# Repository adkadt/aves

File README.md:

<div align="center">

# AVES
### Aerospace Vehicle Embedded Suite

*A personal collection of avionics projects for model rocketry.*

</div>

---

## Overview

AVES is a collection of hardware and software projects developed for model rockets. The goal is to design reliable, flight-ready avionics while documenting the engineering process along the way.

Each project is developed independently and focuses on solving a specific problem, such as flight computers, telemetry, or tracking.

---

## Projects

| Project | Description | Status |
|---------|-------------|--------|
| **Pigeon** | GPS and LoRa tracker for rocket recovery | In Development |
| **Shrike** | Dual-deployment flight computer and altimeter | Early Development |
| **Wren** | Dual-deployment flight computer with integrated IMU and altimeter | Early Development |
| **GPS Ground Station** | Microcontroller-based LoRa receiver for displaying GPS telemetry | In Development |

---

## Goals

- Build reliable avionics for model rockets
- Learn through hands-on embedded development
- Produce well-documented hardware and firmware
- Keep projects maintainable and easy to understand

---

## Technologies

Projects within AVES make use of technologies such as:

- C++
- PlatformIO
- ESP32
- GPS
- LoRa
- Barometric sensors
- IMUs

The exact hardware varies by project.

---

## Repository Layout

```
AVES/
├── gps-ground-station/
├── pigeon/
├── shrike/
├── wren/
└── README.md
```

Each project contains its own firmware and documentation.

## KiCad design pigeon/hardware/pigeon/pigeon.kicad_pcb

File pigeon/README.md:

# Pigeon

Pigeon is a lightweight GPS and LoRa tracker built around the ESP32-S3. It is designed to provide reliable location tracking of landed model rockets.
## Features

- GPS position tracking
- LoRa communication
- Low-power friendly architecture

## Hardware

Current target platform:

- Waveshare ESP32-S3-Zero
- Adafruit Ultimate GPS
- Adafruit LoRa Radio
- WS2812 Status LED

## Project Structure

```
pigeon/
├── firmware/
│   ├── include/
│   ├── src/
│   └── platformio.ini
└── hardware/
```

## Firmware Design

The firmware is organized into independent modules.

- **LED** – Status indication and animations
- **GPS** – Position acquisition and parsing
- **LoRa** – Packet transmission and reception

Each module exposes a small public interface while hiding implementation details internally.

## Building

This project uses PlatformIO.

```bash
cd firmware
pio run
```

To upload:

```bash
pio run --target upload
```

To open the serial monitor:

```bash
pio device monitor
```

## Roadmap

- [x] Project structure
- [x] LED driver
- [ ] GPS integration
- [ ] LoRa communication

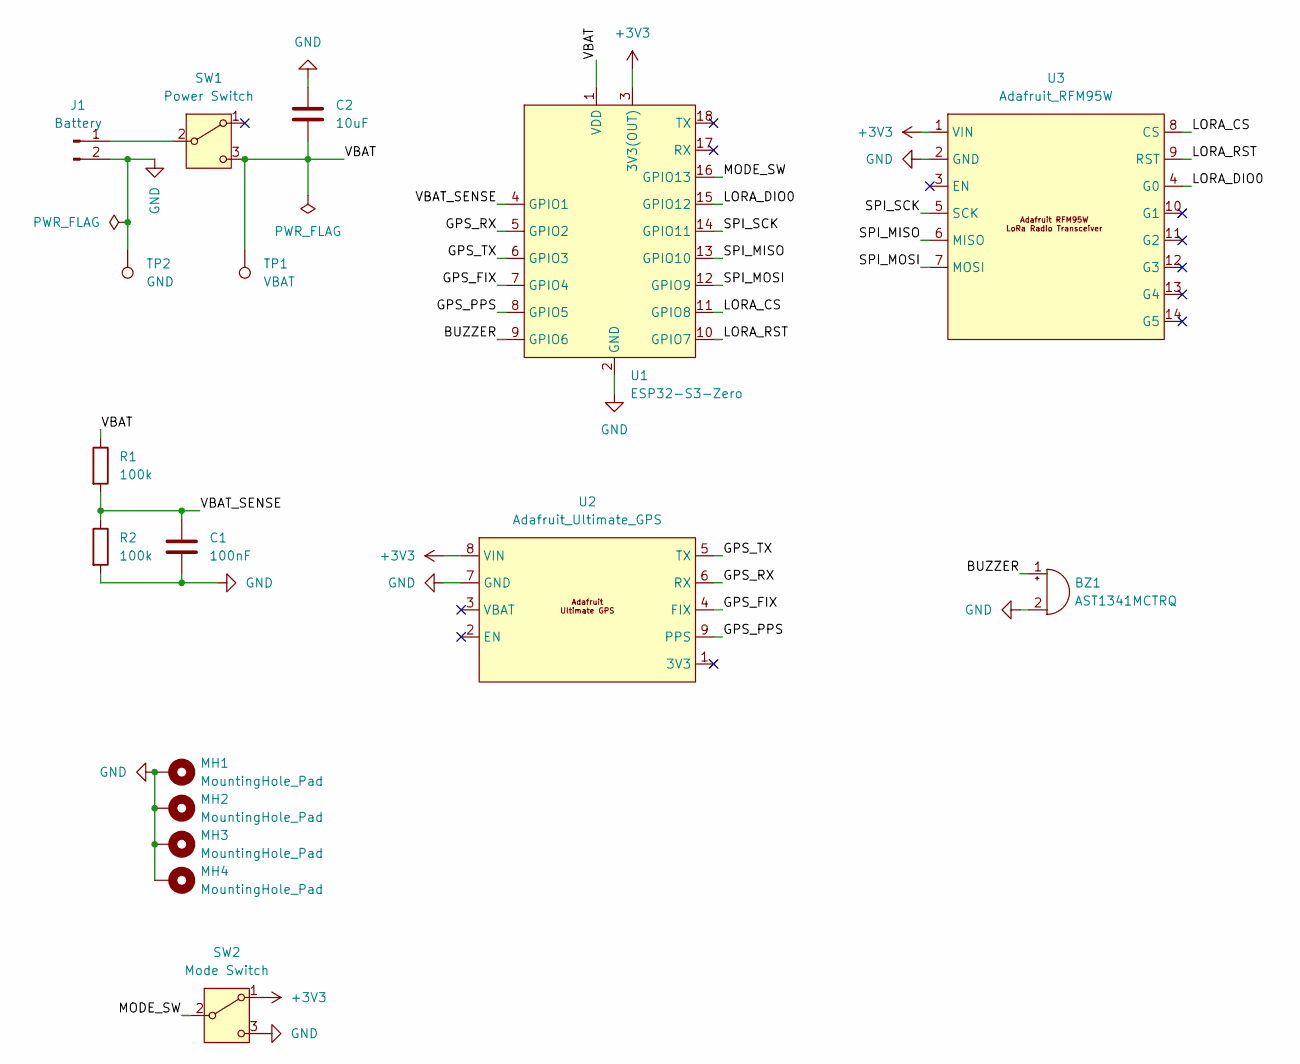
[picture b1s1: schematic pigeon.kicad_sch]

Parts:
BZ1: AST1341MCTRQ; BZ_AST1341MCTRQ
C1: 100nF; C_0805_2012Metric_Pad1.18x1.45mm_HandSolder
C2: 10uF; C_0805_2012Metric_Pad1.18x1.45mm_HandSolder
J1: Battery; JST_PH_S2B-PH-K_1x02_P2.00mm_Horizontal
MH1, MH2, MH3, MH4: MountingHole_Pad; MountingHole_2.2mm_M2_Pad_Via
R1, R2: 100k; R_0805_2012Metric_Pad1.20x1.40mm_HandSolder
SW1: Power Switch; SW_CK_JS102011SAQN
SW2: Mode Switch; SW_CK_JS102011SAQN
TP1: VBAT; TestPoint_Pad_D2.0mm
TP2: GND; TestPoint_Pad_D2.0mm
U1: ESP32-S3-Zero; Waveshare-ESP32-S3-Zero
U2: Adafruit_Ultimate_GPS
U3: Adafruit_RFM95W

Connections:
+3V3: SW2.1 (A), U1.3 (3V3(OUT)), U2.8 (VIN), U3.1 (VIN)
/BUZZER: BZ1.1 (+), U1.9 (GPIO6)
/GPS_FIX: U1.7 (GPIO4), U2.4 (FIX)
/GPS_PPS: U1.8 (GPIO5), U2.9 (PPS)
/GPS_RX: U1.5 (GPIO2), U2.6 (RX)
/GPS_TX: U1.6 (GPIO3), U2.5 (TX)
/LORA_CS: U1.11 (GPIO8), U3.8 (CS)
/LORA_DIO0: U1.15 (GPIO12), U3.4 (G0)
/LORA_RST: U1.10 (GPIO7), U3.9 (RST)
/MODE_SW: SW2.2 (B), U1.16 (GPIO13)
/SPI_MISO: U1.13 (GPIO10), U3.6 (MISO)
/SPI_MOSI: U1.12 (GPIO9), U3.7 (MOSI)
/SPI_SCK: U1.14 (GPIO11), U3.5 (SCK)
/VBAT: C2.2, R1.1, SW1.3 (C), TP1.1 (1_1), U1.1 (VDD)
/VBAT_SENSE: C1.1, R1.2, R2.1, U1.4 (GPIO1)
GND: BZ1.2 (-), C1.2, C2.1, J1.2, MH1.1 (1_1), MH2.1 (1_1), MH3.1 (1_1), MH4.1 (1_1), R2.2, SW2.3 (C), TP2.1 (1_1), U1.2 (GND), U2.7 (GND), U3.2 (GND)
unnamed: J1.1, SW1.2 (B)

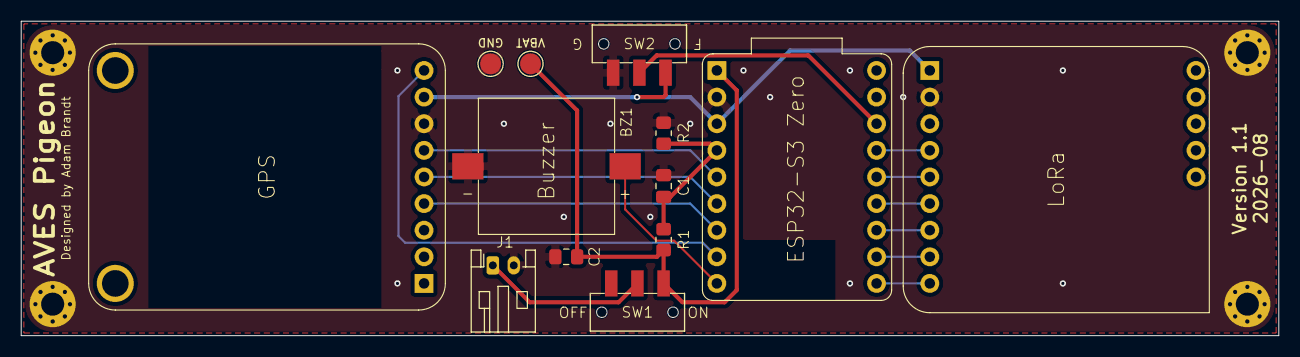
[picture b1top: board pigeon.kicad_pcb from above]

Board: 2 copper layers, 120.0 x 30.0 mm, 17 parts (0 on the bottom side), 17 nets.

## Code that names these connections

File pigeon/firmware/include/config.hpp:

#pragma once

#include <cstdint>
#include "system/system.hpp"

namespace Config {
    // This hardware revision has no physical mode switch.
    constexpr bool MODE_SWITCH_ENABLED = false;
    constexpr System::Mode PRIMARY_MODE = System::Mode::FLIGHT; // FLIGHT
    constexpr System::Mode SECONDARY_MODE = System::Mode::GROUND; // GROUND

    // Serial Config
    constexpr uint32_t BAUD_RATE = 115200;

    constexpr uint8_t DEVICE_ID = 1;
    constexpr uint8_t PAIRED_DEVICE_ID = 2;
    
    // GPS Config
    namespace GPS {
        constexpr uint32_t BAUD_RATE = 9600;
        constexpr uint32_t TIMEOUT_MS = 3000;
    
        // EMA
        constexpr double POSITION_ALPHA = 0.25;
    }

    // LoRa Config
    namespace LoRa {
        constexpr uint8_t MAX_PAYLOAD_LENGTH = 64;
        constexpr uint8_t PACKET_HEADER_LENGTH = 5; // this value is based on code [don't change]
        constexpr uint8_t MAX_PACKET_LENGTH = LoRa::MAX_PAYLOAD_LENGTH + LoRa::PACKET_HEADER_LENGTH;
    
        // LoRa Radio
        constexpr float FREQUENCY = 915.0;
        constexpr float BANDWIDTH = 125.0;
        constexpr uint8_t SPREADING_FACTOR = 9;
        constexpr uint8_t CODING_RATE = 7;
        constexpr uint8_t SYNC_WORD = 0x12;
        constexpr int8_t TX_POWER = 10;
        constexpr uint8_t PREAMBLE_LENGTH = 8;
        constexpr uint8_t GAIN = 0;
    } 

    // Battery
    namespace Battery {
        // Voltage divider
        constexpr float DIVIDER_TOP_RESISTOR = 100000.0f;
        constexpr float DIVIDER_BOTTOM_RESISTOR = 100000.0f;
        
        // Sampling
        constexpr uint32_t SAMPLE_INTERVAL_MS = 100; 

        // Battery Thresholds
        constexpr float MIN_USB_VOLTAGE = 4.7f;
        constexpr float LOW_VOLTAGE = 3.6f;
        constexpr float CRITICAL_VOLTAGE = 3.3f;
        constexpr float MEASURE_THRESHOLD_VOLTAGE = 1.0f;

        // EMA
        constexpr float VOLTAGE_FILTER_ALPHA  = 0.3f;
    }

    namespace Flight {
        constexpr uint32_t HEARTBEAT_INTERVAL = 15000;
        constexpr uint32_t GPS_TELEMETRY_INTERVAL = 1000;
    }

    namespace Ground {
        constexpr uint32_t CONNECTION_TIMEOUT = 60000;
    }
}

namespace Pins {
    // LED
    constexpr uint8_t LED = 21;
    
    // GPS
    constexpr uint8_t GPS_RX = 2;
    constexpr uint8_t GPS_TX = 3;
    constexpr uint8_t GPS_FIX = 4;
    constexpr uint8_t GPS_PPS = 5;   
    
    // LoRa
    constexpr uint8_t LORA_SCK = 11;
    constexpr uint8_t LORA_MISO = 10;
    constexpr uint8_t LORA_MOSI = 9;
    constexpr uint8_t LORA_CS = 8;
    constexpr uint8_t LORA_RST = 7;
    constexpr uint8_t LORA_DIO0 = 12; // G0, IRQ/ DIO0

    // Misc
    constexpr uint8_t VBAT_SENSE = 1;
    constexpr uint8_t BUZZER = 6;
    constexpr uint8_t MODE_SWITCH = 13;
}

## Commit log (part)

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2026-05-15 added state logic
2026-05-18 Setup altimeter class with circular ring buffer to calculate a moving average of the ground altitude
2026-05-18 Integrate Altitude class and add some state logic before parachute deployment
2026-05-18 Added data logging to SD card
2026-05-20 added counter for lockout of ground buffer
2026-05-20 added state leds and simulation mode to accept a stream of altitude instead of bmp
2026-05-20 Split main into datalogger and flight controller
2026-05-20 added buzzer
2026-05-20 adjusted check for minimum altitude for deployment
2026-05-20 added error check
2026-05-20 update simulation mode name
